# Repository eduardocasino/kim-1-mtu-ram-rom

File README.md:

# KIM-1 RAM/ROM Expansion Board for the MTU Backplane

## **WARNING**

**ALTHOUGH THE REV. 3 SEEMS TO BE WORKING SO FAR, IT STILL NEEDS MORE TESTING. USE AT YOUR OWN RISK!!!**

If you ordered the first or second revision PCB, please see the "Rev. 1 Fix" and/or "Rev. 2 Fix" sections below.

## About

This is a highly configurable RAM/ROM expansion for MTU backplanes, like the one in the original K-1005 card file, my [expansion card](https://github.com/eduardocasino/kim-1-mtu-expansion-card) or my buffered motherboard.

WARNING: This design has not been tested yet. Use at your own risk!

## Characteristics

* Switchable 0000-03FF systen RAM replacement
* Switchable 0400-13FF RAM
* Switchable system ROM replacement (needs a small modification to the MTU boards to disable the DECEN line)
* 4 selectable ROM sets
* Enough room to place a ZIF socket for the ROM
* Switchable 4K RAM/ROM areas from 2000 to FFFF
* Configurable interrupt vectors to the top of any of the 4K chunks.
* Max. 1 TTL load on the bus, so it will work nicely on unbuffered backplanes

## Licensing

This is a personal project that I am sharing in case it is of interest to any retrocomputing enthusiast and all the information in this repository is provided "as is", without warranty of any kind. I am not liable for any damages that may occur, whether it be to individuals, objects, KIM-1 computers, kittens or any other pets. **It should also be noted that everything in this repository is a work in progress, has not been tested and may contain errors, therefore anyone who chooses to use it does so at their own risk**.

This work is licensed under a [Creative Commons Attribution-ShareAlike 4.0 International License](http://creativecommons.org/licenses/by-sa/4.0/).

See the LICENSE.md file for details.

## Rev. 2 Fix

Replacing the system RAM (0x0000-0x03FF) does not work reliably with the revision 2 PCB.

There is a simple fix with a couple of bodges:

Using a cutter, carefully cut the tracks that joins pin 24 of U1 and pin 16 of U2:

On the back side, cut the spoke at pin 24 of U1 (not strictly needed, but it is better to not have that copper island attached to the pin) and the track that joins pin 29 of U1 and pad 'V' of the edge connector:

Finally, solder these two wires:

## Rev. 1 Fix

If you built revision 1 of this board, you may have found out that the 0400-13FF RAM does not work with the [buffered motherboard](https://github.com/eduardocasino/kim-1-mtu-motherboard). It works fine with the [passive expansion board](https://github.com/eduardocasino/kim-1-mtu-expansion-card) and it should also work in a real MTU cabinet (See [Issue #1](https://github.com/eduardocasino/kim-1-mtu-ram-rom/issues/1))

You can perform this very simple bodge on the the PCB:

Using a cutter, carefully cut the track that joins pins 1 and 4 of U6 on the front side of the PCB:

Now on the back side, cut these spokes at pins 12 and 13 of the same IC:

Finally, solder these three wires:

## Changelog
#### 30/04/2024
* Release Rev. 3
* Fix replacing system RAM
#### 28/01/2024
* Release Rev. 2
* Fix [Issue #1](https://github.com/eduardocasino/kim-1-mtu-ram-rom/issues/1)
* Add new option for replacing system RAM
* Make some more space for the ZIF socket lever
* Add instructions to fix Rev. 1 boards.
#### 05/01/2024
* Minor silkscreen modifications
#### 26/11/2023
* Remove useless option to support the MTU floppy controller boot prom
* Simplify design a bit
#### 24/11/2023
* Add option to support the MTU floppy controller boot prom
* Minor silkscreen update

## Acknowledgements

* This design is based on late Bob Applegate's [60K RAM/ROM card](https://www.corshamtech.com/product/kim-1-60k-rameprom-board/)

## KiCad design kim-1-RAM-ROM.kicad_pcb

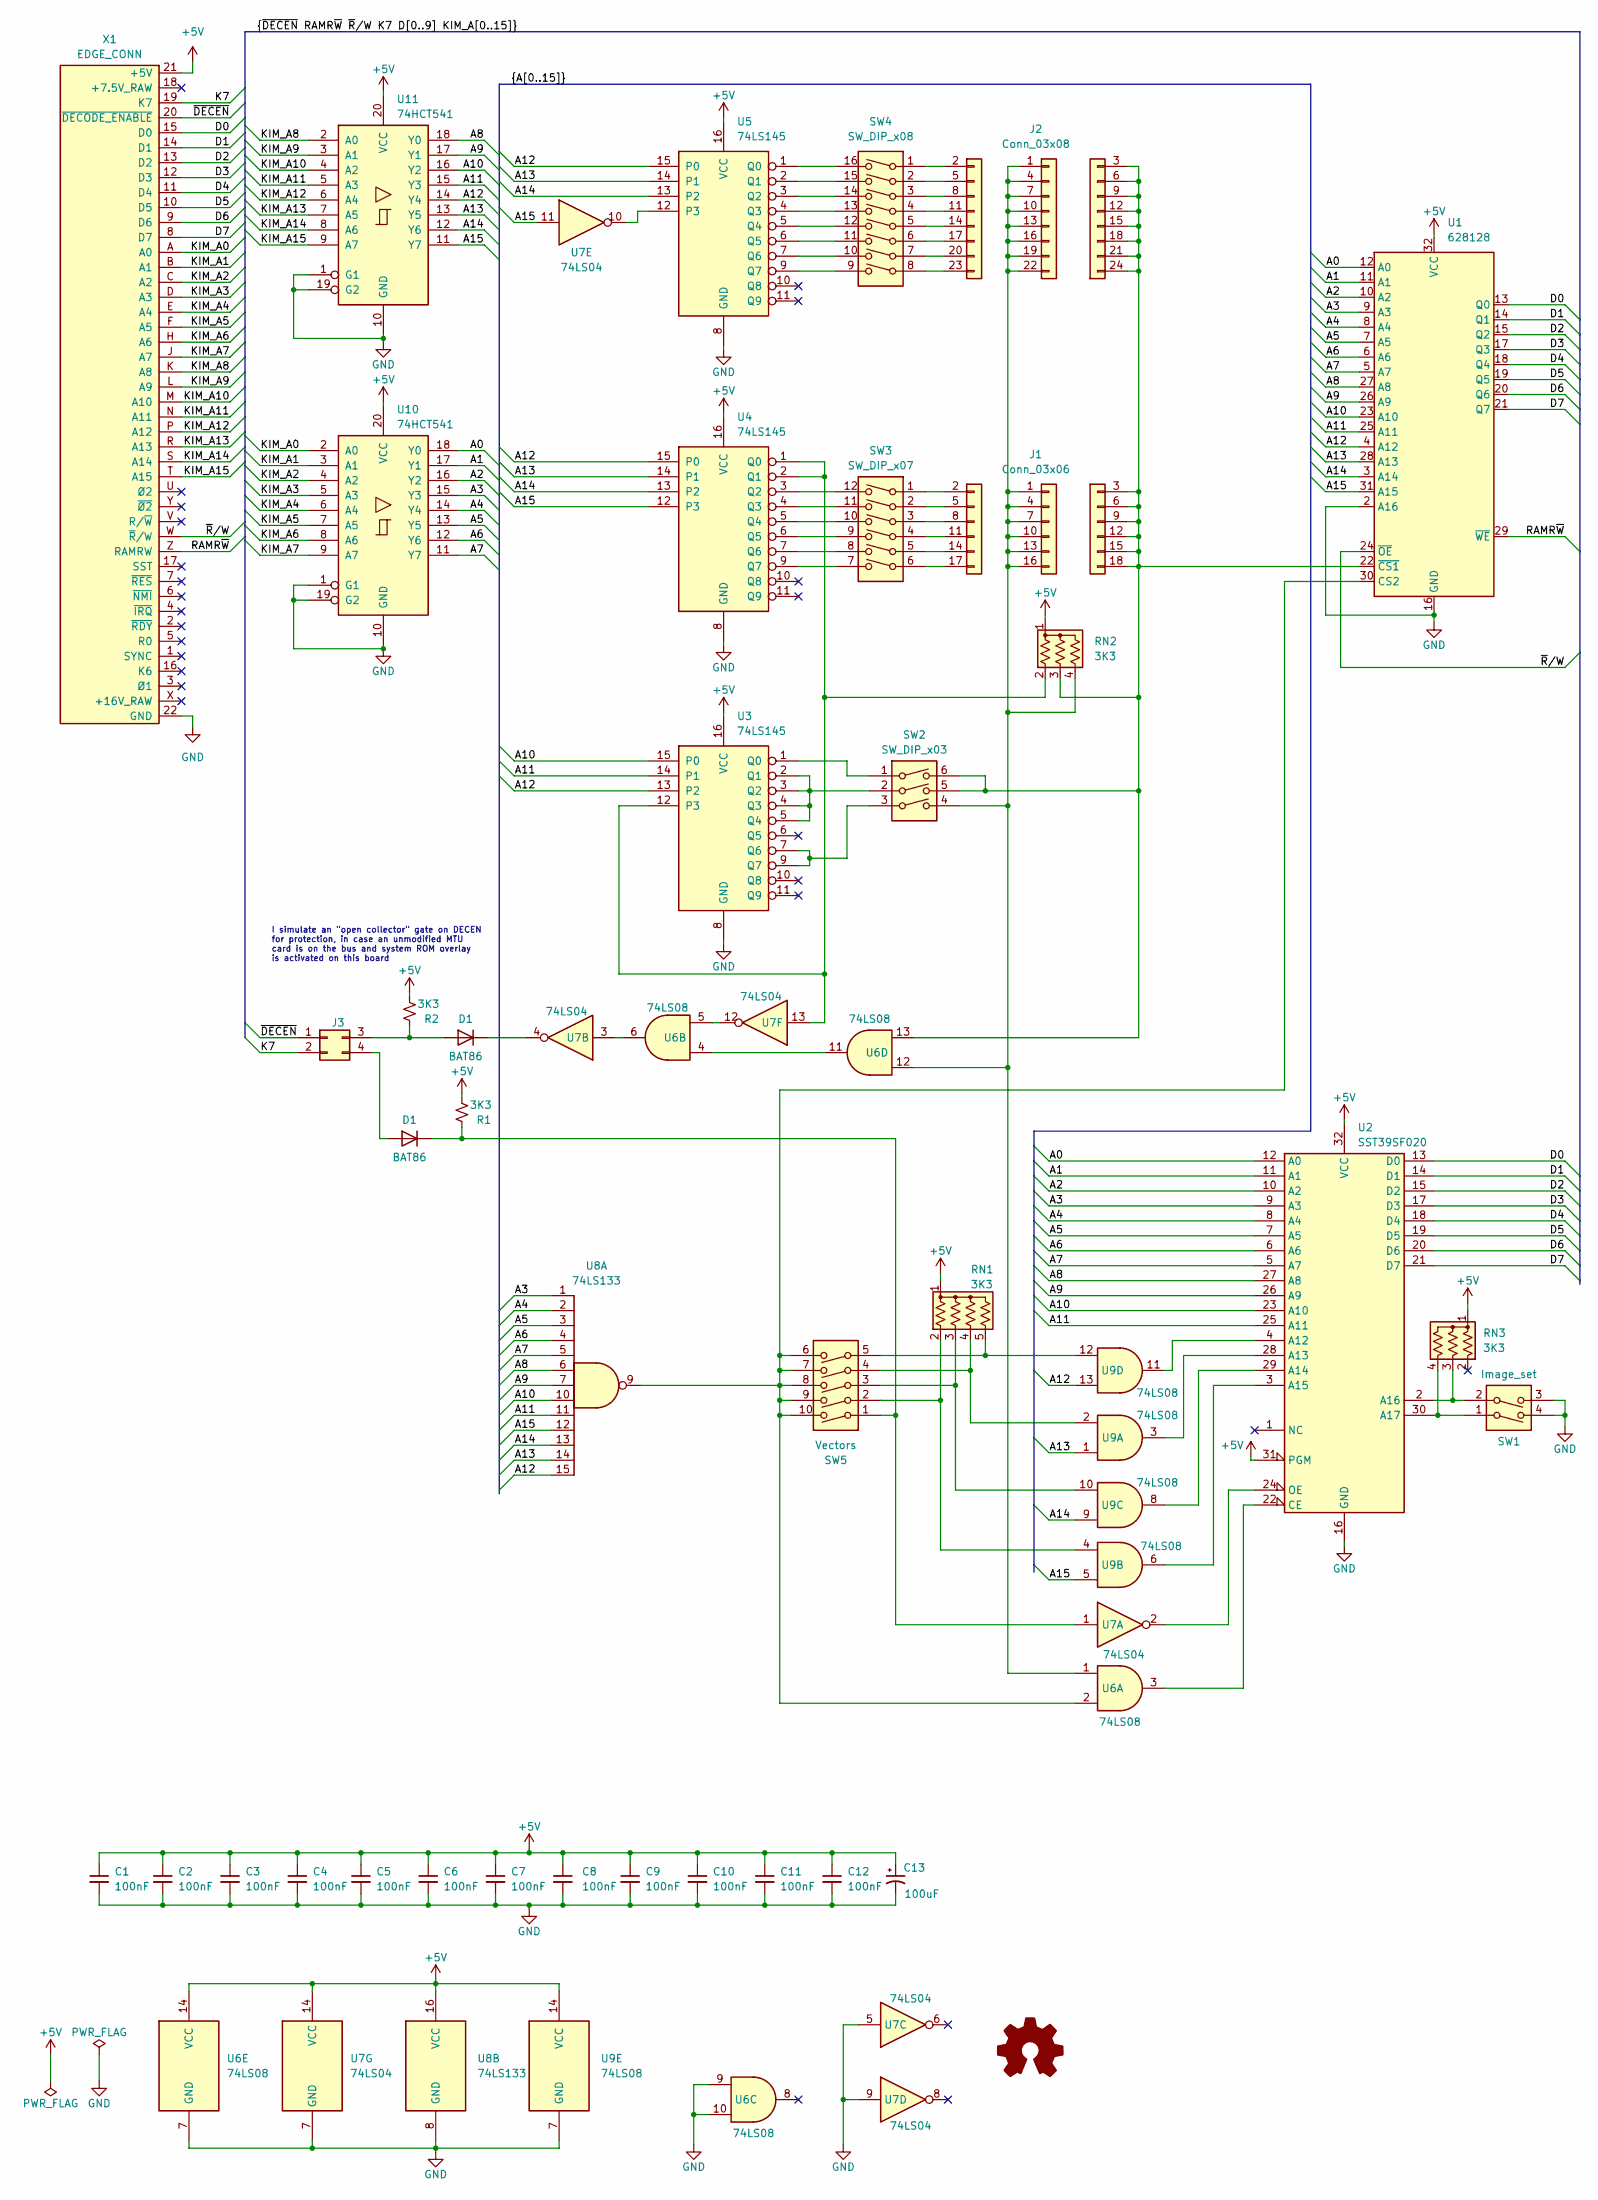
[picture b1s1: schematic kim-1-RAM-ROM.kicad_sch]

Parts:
C1, C2, C3, C4, C5, C6, C7, C8, C9, C10, C11, C12: 100nF; C_Disc_D5.0mm_W2.5mm_P5.00mm
C13: 100uF; CP_Radial_D6.3mm_P2.50mm
D1: BAT86; D_DO-35_SOD27_P7.62mm_Horizontal
J1: Conn_03x06; PinHeader_3x06_P2.54mm_Vertical
J2: Conn_03x08; PinHeader_3x08_P2.54mm_Vertical
J3: Conn_02x08_Counter_Clockwise; PinHeader_2x02_P2.54mm_Vertical
R1, R2: 3K3; R_Axial_DIN0207_L6.3mm_D2.5mm_P7.62mm_Horizontal
RN1: 3K3; R_Array_SIP5
RN2, RN3: 3K3; R_Array_SIP4
SW1: Image_set; SW_DIP_SPSTx02_Slide_9.78x7.26mm_W7.62mm_P2.54mm
SW2: SW_DIP_x03; SW_DIP_SPSTx03_Slide_9.78x9.8mm_W7.62mm_P2.54mm
SW3: SW_DIP_x07; SW_DIP_SPSTx06_Slide_9.78x17.42mm_W7.62mm_P2.54mm
SW4: SW_DIP_x08; SW_DIP_SPSTx08_Slide_9.78x22.5mm_W7.62mm_P2.54mm
SW5: Vectors; SW_DIP_SPSTx05_Slide_9.78x14.88mm_W7.62mm_P2.54mm
U1: 628128; DIP-32_W15.24mm_LongPads
U2: SST39SF020; DIP_Socket-32_W11.9_W12.7_W15.24_W17.78_W18.5_3M_232-1285-0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
U3, U4, U5: 74LS145; DIP-16_W7.62mm_LongPads
U6, U9: 74LS08; DIP-14_W7.62mm_LongPads
U7: 74LS04; DIP-14_W7.62mm_LongPads
U8: 74LS133; DIP-16_W7.62mm_LongPads
U10, U11: 74HCT541; DIP-20_W7.62mm_LongPads
X1: EDGE_CONN

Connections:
+5V: C1.1, C2.1, C3.1, C4.1, C5.1, C6.1, C7.1, C8.1, C9.1, C10.1, C11.1, C12.1, C13.1, R1.2, R2.2, RN1.1 (common), RN2.1 (common), RN3.1 (common), U1.32 (VCC), U2.31 (PGM), U2.32 (VCC), U3.16 (VCC), U4.16 (VCC), U5.16 (VCC), U6.14 (VCC), U7.14 (VCC), U8.16 (VCC), U9.14 (VCC), U10.20 (VCC), U11.20 (VCC), X1.21 (+5V)
/A0: U1.12 (A0), U2.12 (A0), U10.18 (Y0)
/A1: U1.11 (A1), U2.11 (A1), U10.17 (Y1)
/A2: U1.10 (A2), U2.10 (A2), U10.16 (Y2)
/A3: U1.9 (A3), U2.9 (A3), U8.1, U10.15 (Y3)
/A4: U1.8 (A4), U2.8 (A4), U8.2, U10.14 (Y4)
/A5: U1.7 (A5), U2.7 (A5), U8.3, U10.13 (Y5)
/A6: U1.6 (A6), U2.6 (A6), U8.4, U10.12 (Y6)
/A7: U1.5 (A7), U2.5 (A7), U8.5, U10.11 (Y7)
/A8: U1.27 (A8), U2.27 (A8), U8.6, U11.18 (Y0)
/A9: U1.26 (A9), U2.26 (A9), U8.7, U11.17 (Y1)
/A10: U1.23 (A10), U2.23 (A10), U3.15 (P0), U8.10, U11.16 (Y2)
/A11: U1.25 (A11), U2.25 (A11), U3.14 (P1), U8.11, U11.15 (Y3)
/A12: U1.4 (A12), U3.13 (P2), U4.15 (P0), U5.15 (P0), U8.15, U9.13, U11.14 (Y4)
/A13: U1.28 (A13), U4.14 (P1), U5.14 (P1), U8.14, U9.1, U11.13 (Y5)
/A14: U1.3 (A14), U4.13 (P2), U5.13 (P2), U8.13, U9.9, U11.12 (Y6)
/A15: U1.31 (A15), U4.12 (P3), U7.11, U8.12, U9.5, U11.11 (Y7)
/D0: U1.13 (Q0), U2.13 (D0), X1.15 (D0)
/D1: U1.14 (Q1), U2.14 (D1), X1.14 (D1)
/D2: U1.15 (Q2), U2.15 (D2), X1.13 (D2)
/D3: U1.17 (Q3), U2.17 (D3), X1.12 (D3)
/D4: U1.18 (Q4), U2.18 (D4), X1.11 (D4)
/D5: U1.19 (Q5), U2.19 (D5), X1.10 (D5)
/D6: U1.20 (Q6), U2.20 (D6), X1.9 (D6)
/D7: U1.21 (Q7), U2.21 (D7), X1.8 (D7)
/K7: J3.2, X1.19 (K7)
/KIM_A0: U10.2 (A0), X1.A (A0)
/KIM_A1: U10.3 (A1), X1.B (A1)
/KIM_A2: U10.4 (A2), X1.C (A2)
/KIM_A3: U10.5 (A3), X1.D (A3)
/KIM_A4: U10.6 (A4), X1.E (A4)
/KIM_A5: U10.7 (A5), X1.F (A5)
/KIM_A6: U10.8 (A6), X1.H (A6)
/KIM_A7: U10.9 (A7), X1.J (A7)
/KIM_A8: U11.2 (A0), X1.K (A8)
/KIM_A9: U11.3 (A1), X1.L (A9)
/KIM_A10: U11.4 (A2), X1.M (A10)
/KIM_A11: U11.5 (A3), X1.N (A11)
/KIM_A12: U11.6 (A4), X1.P (A12)
/KIM_A13: U11.7 (A5), X1.R (A13)
/KIM_A14: U11.8 (A6), X1.S (A14)
/KIM_A15: U11.9 (A7), X1.T (A15)
/RAMR~W: U1.29 (~WE), X1.Z (RAMRW)
/~DECEN: J3.1, X1.20 (~DECODE_ENABLE)
/~R/W: U1.24 (~OE), X1.W (~R/W)
GND: C1.2, C2.2, C3.2, C4.2, C5.2, C6.2, C7.2, C8.2, C9.2, C10.2, C11.2, C12.2, C13.2, SW1.3, SW1.4, U1.2 (A16), U1.16 (GND), U2.16 (GND), U3.8 (GND), U4.8 (GND), U5.8 (GND), U6.7 (GND), U6.9, U6.10, U7.5, U7.7 (GND), U7.9, U8.8 (GND), U9.7 (GND), U10.1 (G1), U10.10 (GND), U10.19 (G2), U11.1 (G1), U11.10 (GND), U11.19 (G2), X1.22 (GND)
unnamed: J1.1, J1.4, J1.7, J1.10, J1.13, J1.16, J2.1, J2.4, J2.7, J2.10, J2.13, J2.16, J2.19 (Pin_º9), J2.22, RN2.4 (R3), SW2.4, U6.1, U6.12
unnamed: J1.2, SW3.1
unnamed: J1.5, SW3.2
unnamed: J1.8, SW3.3
unnamed: J1.11, SW3.4
unnamed: J1.3, J1.6, J1.9, J1.12, J1.15, J1.18, J2.3, J2.6, J2.9, J2.12, J2.15, J2.18, J2.21, J2.24, RN2.3 (R2), SW2.5, SW2.6, U1.22 (~CS1), U6.13
unnamed: J1.14, SW3.5
unnamed: J1.17, SW3.6
unnamed: J2.2, SW4.1
unnamed: J2.5, SW4.2
unnamed: J2.8, SW4.3
unnamed: J2.11, SW4.4
unnamed: J2.14, SW4.5
unnamed: J2.17, SW4.6
unnamed: J2.20, SW4.7
unnamed: J2.23, SW4.8
unnamed: RN1.2 (R1), SW5.2, U9.4
unnamed: RN1.3 (R2), SW5.3, U9.10
unnamed: RN1.4 (R3), SW5.4, U9.2
unnamed: RN1.5 (R4), SW5.5, U9.12
unnamed: RN2.2 (R1), U3.12 (P3), U4.1 (Q0), U4.2 (Q1), U7.13
unnamed: RN3.3 (R2), SW1.2, U2.2 (A16)
unnamed: RN3.4 (R3), SW1.1, U2.30 (A17)
unnamed: SW5.6, SW5.7, SW5.8, SW5.9, SW5.10, U1.30 (CS2), U6.2, U8.9
unnamed: U2.4 (A12), U9.11
unnamed: U2.28 (A13), U9.3
unnamed: U2.29 (A14), U9.8
unnamed: U2.3 (A15), U9.6
unnamed: U2.22 (CE), U6.3
unnamed: U2.24 (OE), U7.2
unnamed: SW2.1, U3.1 (Q0)
unnamed: SW2.2, U3.2 (Q1), U3.3 (Q2), U3.4 (Q3), U3.5 (Q4)
unnamed: SW2.3, U3.7 (Q6), U3.9 (Q7)
unnamed: SW3.12, U4.3 (Q2)
unnamed: SW3.11, U4.4 (Q3)
unnamed: SW3.10, U4.5 (Q4)
unnamed: SW3.9, U4.6 (Q5)
unnamed: SW3.8, U4.7 (Q6)
unnamed: SW3.7, U4.9 (Q7)
unnamed: U5.12 (P3), U7.10
unnamed: SW4.16, U5.1 (Q0)
unnamed: SW4.15, U5.2 (Q1)
unnamed: SW4.14, U5.3 (Q2)
unnamed: SW4.13, U5.4 (Q3)
unnamed: SW4.12, U5.5 (Q4)
unnamed: SW4.11, U5.6 (Q5)
unnamed: SW4.10, U5.7 (Q6)
unnamed: SW4.9, U5.9 (Q7)
unnamed: U6.5, U7.12
unnamed: U6.6, U7.3
unnamed: U6.4, U6.11

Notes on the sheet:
I simulate an "open collector" gate on DECEN for protection, in case an unmodified MTU card is on the bus and system ROM overlay is activated on this board

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
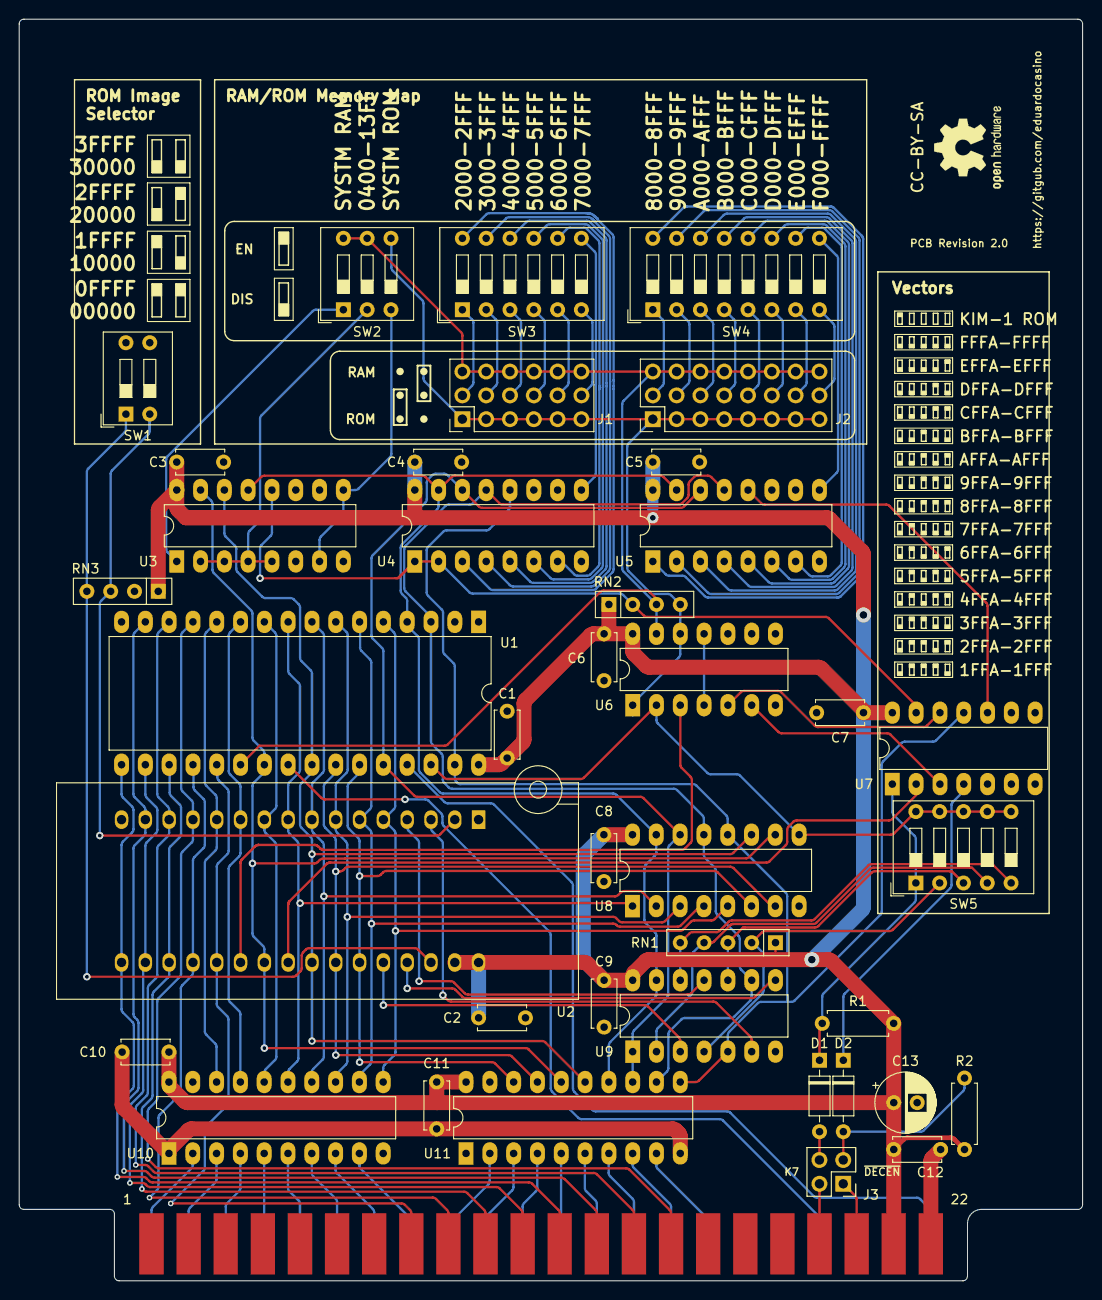
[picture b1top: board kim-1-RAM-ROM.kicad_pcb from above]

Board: 2 copper layers, 113.5 x 134.6 mm, 40 parts (0 on the bottom side), 101 nets.

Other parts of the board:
D2: BAT86; D_DO-35_SOD27_P7.62mm_Horizontal

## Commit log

2023-11-18 Fix image links
2023-11-24 Add option to support the MTU floppy controller boot prom
2023-11-24 Minor silkscreen changes
2023-11-26 Remove useless switch and simplify design
2024-01-23 Add credits for DIP switches 3d models
2024-01-28 Release 2.0. Fixes issue #1
2024-01-28 Clarify when rev. 1 does not work
2024-04-30 Fix replacing system RAM

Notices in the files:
README.md:
Licensing:
[CC BY-SA 4.0](http:
CC BY-SA 4.0
kim-1-RAM-ROM.kicad_pcb:
CC-BY-SA
